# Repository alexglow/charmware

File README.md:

# charmware
modular tech jewelry // pcbs for building custom wearable electronic circuits. Check out the full write-up at http://bit.ly/charmware !  
Most recent versions on OSH Park:  
* [Dyson](https://oshpark.com/shared_projects/vTxQnrnv) (power: CR1225 coin cell battery)
* [Star](https://oshpark.com/shared_projects/OCLaUlSm) (multipurpose for through-hole or 1206 SMD components: LED, resistor, reed switch, button, ...)

## usage
I would recommend NOT building these yet, since they will go through a few more iterations before I'm comfortable encouraging others to use them. But feel free to download, for your own curiosity or to play around with! <3

## fab guidelines
Recommend ordering these in half-height (0.8mm) from Osh Park. :)

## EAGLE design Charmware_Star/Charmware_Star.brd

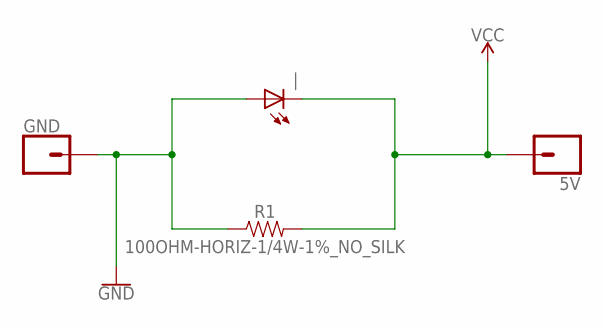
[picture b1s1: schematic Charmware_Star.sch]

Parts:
5V: CONN_01PTH_NO_SILK_YES_STOP; 1X01_NO_SILK
GND: CONN_01PTH_NO_SILK_YES_STOP; 1X01_NO_SILK
R1: 100OHM-HORIZ-1/4W-1%_NO_SILK; AXIAL-0.3-NO_SILK
|: LEDSMT1206; 1206

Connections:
5V: 5V.1, R1.P$2 (2), |.C
GND: GND.1, R1.P$1 (1), |.A

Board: 2 copper layers, 4 parts (0 on the bottom side), 2 nets, no tracks yet.

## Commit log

2018-05-17 first files and readme

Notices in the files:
parts and their libraries:
SparkFun-Resistors: Licensing: Creative Commons ShareAlike 4.0 International - https://creativecommons.org/licenses/by-sa/4.0
